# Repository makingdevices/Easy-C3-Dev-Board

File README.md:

<!-- Improved compatibility of back to top link: See: https://github.com/othneildrew/Best-README-Template/pull/73 -->

<!--
*** Thanks for checking out the Best-README-Template. If you have a suggestion
*** that would make this better, please fork the repo and create a pull request
*** or simply open an issue with the tag "enhancement".
*** Don't forget to give the project a star!
*** Thanks again! Now go create something AMAZING! :D
-->

<!-- PROJECT SHIELDS -->
<!--
*** I'm using markdown "reference style" links for readability.
*** Reference links are enclosed in brackets [ ] instead of parentheses ( ).
*** See the bottom of this document for the declaration of the reference variables
*** for contributors-url, forks-url, etc. This is an optional, concise syntax you may use.
*** https://www.markdownguide.org/basic-syntax/#reference-style-links
-->
[![Instagram][ig-shield]][ig-url]
[![PCBWAY][sponsor-shield]][sponsor-url]
[![Stargazers][stars-shield]][stars-url]
[![Issues][issues-shield]][issues-url]
[![LinkedIn][linkedin-shield]][linkedin-url]

<!-- PROJECT LOGO -->
<br />
<div align="center">

<h3 align="center">Making Devices</h3>

  <p align="center">
    Open Source projects where we struggle with engineering, electronics, coding and who knows what else... In this case, The Easy C3 Dev Board is a development board for the esp32 C3 so I can test their capabilities, so hopefully you may find it interesting ;)
  </p>
</div>

<!-- TABLE OF CONTENTS -->
<details>
  <summary>Table of Contents</summary>
  <ol>
    <li>
      <a href="#about-the-project">About The Project</a>
      <ul>
        <li><a href="#built-with">Built With</a></li>
      </ul>
    </li>
    <li>
      <a href="#Build-one">Build one</a>
      <ul>
      </ul>
    </li>
    <li><a href="#usage">Usage</a></li>
    <li><a href="#roadmap">Roadmap</a></li>
    <li><a href="#license">License</a></li>
    <li><a href="#contact">Contact</a></li>
    <li><a href="#Sponsor">Sponsor</a></li>
  </ol>
</details>

<!-- ABOUT THE PROJECT -->
## About The Project

[![Bytes Counter Shot][product-screenshot]](https://github.com/makingdevices/Easy-C3-Dev-Board)

The Easy C3 Dev Board is a esp32 C3 based development board to test this microcontroller.

This device is under development, so I do encourage you to not assembly, order any PCB or use any software from this repository until the project is finished.

<p align="right">(<a href="#readme-top">back to top</a>)</p>

### Built With

[![Kicad][kicad-shield]][kicad-url]
[![SPONSOR][sponsor-icon]][sponsor-url]

<p align="right">(<a href="#readme-top">back to top</a>)</p>

<!-- GETTING STARTED -->

## Build one
NOT RECOMMENDED AS THE DEVICE IS UNDER DEVELOPMENT

<p align="right">(<a href="#readme-top">back to top</a>)</p>

<!-- USAGE EXAMPLES -->
## Usage

Instructions of use:

- Not tested

<p align="right">(<a href="#readme-top">back to top</a>)</p>

<!-- ROADMAP -->
## Roadmap

- [ ] Assembly project.
- [ ] Test/validate the board

See the [open issues](https://github.com/makingdevices/Easy-C3-Dev-Board/issues) for a full list of proposed features (and known issues).

State: Project <b>UNFINISHED</b> - 08/01/2023

Priority: <b>Medium</b>

<p align="right">(<a href="#readme-top">back to top</a>)</p>

<!-- LICENSE -->
## License

Distributed under three licenses:
- [Hardware](/License/HW_cern_ohl_s_v2.pdf)
- [Software](/License/SW_GPLv3.0.txt)
- [Documentation](/License/Documentation_CC-BY-SA-4.0.txt)

[![GPL v3 License][license-shield]][license-url] 
<p align="right">(<a href="#readme-top">back to top</a>)</p>

<!-- CONTACT -->
## Contact

Making Devices - [@MakingDevices](https://www.instagram.com/makingdevices/)

Project Link: [https://github.com/makingdevices/OpenReflowPlate](https://github.com/makingdevices/Easy-C3-Dev-Board/)

Other Links: [LinkTree](https://makingdevices.com/links/)

<p align="right">(<a href="#readme-top">back to top</a>)</p>

<!-- MARKDOWN LINKS & IMAGES -->
<!-- https://www.markdownguide.org/basic-syntax/#reference-style-links -->
[contributors-shield]: https://img.shields.io/github/contributors/makingdevices/Easy-C3-Dev-Board.svg?style=for-the-badge
[contributors-url]: https://github.com/makingdevices/Easy-C3-Dev-Board/graphs/contributors
[forks-shield]: https://img.shields.io/github/forks/makingdevices/Easy-C3-Dev-Board.svg?style=for-the-badge
[forks-url]: https://github.com/makingdevices/Easy-C3-Dev-Board/network/members
[stars-shield]: https://img.shields.io/github/stars/makingdevices/Easy-C3-Dev-Board.svg?style=for-the-badge
[stars-url]: https://github.com/makingdevices/Easy-C3-Dev-Board/stargazers
[issues-shield]: https://img.shields.io/github/issues/makingdevices/Easy-C3-Dev-Board.svg?style=for-the-badge
[issues-url]: https://github.com/makingdevices/Easy-C3-Dev-Board/issues
[license-shield]: /images/license.png
[license-url]: https://github.com/makingdevices/Easy-C3-Dev-Board/tree/main/License
[linkedin-shield]: https://img.shields.io/badge/-LinkedIn-black.svg?style=for-the-badge&logo=linkedin&colorB=555
[linkedin-url]: https://www.linkedin.com/company/making-devices/
[sponsor-shield]: https://img.shields.io/badge/SPONSOR-PCBWAY-black.svg?style=for-the-badge&colorB=1200
[sponsor-url]: https://www.pcbway.com/?from=makingdevices
[sponsor-screenshot]: /images/PCB_sponsor.png
[product-screenshot]: images/screenshot.jpg
[PIC]: https://img.shields.io/badge/PIC18LF45K50-000000?style=for-the-badge
[PIC-url]: http://ww1.microchip.com/downloads/en/devicedoc/40001350f.pdf
[kicad-shield]: https://img.shields.io/badge/kicad-0b03fc?style=for-the-badge&logo=kicad&logoColor=white
[kicad-url]: https://www.kicad.org/
[YT-screenshot]: images/YT_assembly.PNG
[sponsor-icon]:  https://img.shields.io/badge/-PCBWAY-black.svg?style=for-the-badge&colorB=1200
[ig-shield]: https://img.shields.io/badge/instagram-a83297?style=for-the-badge&logo=instagram&logoColor=white
[ig-url]: https://www.instagram.com/makingdevices/
[MPLAB-C]: https://img.shields.io/badge/MPLAB%20C18-DD0031?style=for-the-badge&logo=C&logoColor=white
[MPLAB-C-url]: https://www.microchip.com/en-us/development-tool/SW006011
[Svelte.dev]: https://img.shields.io/badge/Svelte-4A4A55?style=for-the-badge&logo=svelte&logoColor=FF3E00
[Svelte-url]: https://svelte.dev/
[Laravel.com]: https://img.shields.io/badge/Laravel-FF2D20?style=for-the-badge&logo=laravel&logoColor=white
[Laravel-url]: https://laravel.com
[Bootstrap.com]: https://img.shields.io/badge/Bootstrap-563D7C?style=for-the-badge&logo=bootstrap&logoColor=white
[Bootstrap-url]: https://getbootstrap.com
[JQuery.com]: https://img.shields.io/badge/jQuery-0769AD?style=for-the-badge&logo=jquery&logoColor=white
[JQuery-url]: https://jquery.com

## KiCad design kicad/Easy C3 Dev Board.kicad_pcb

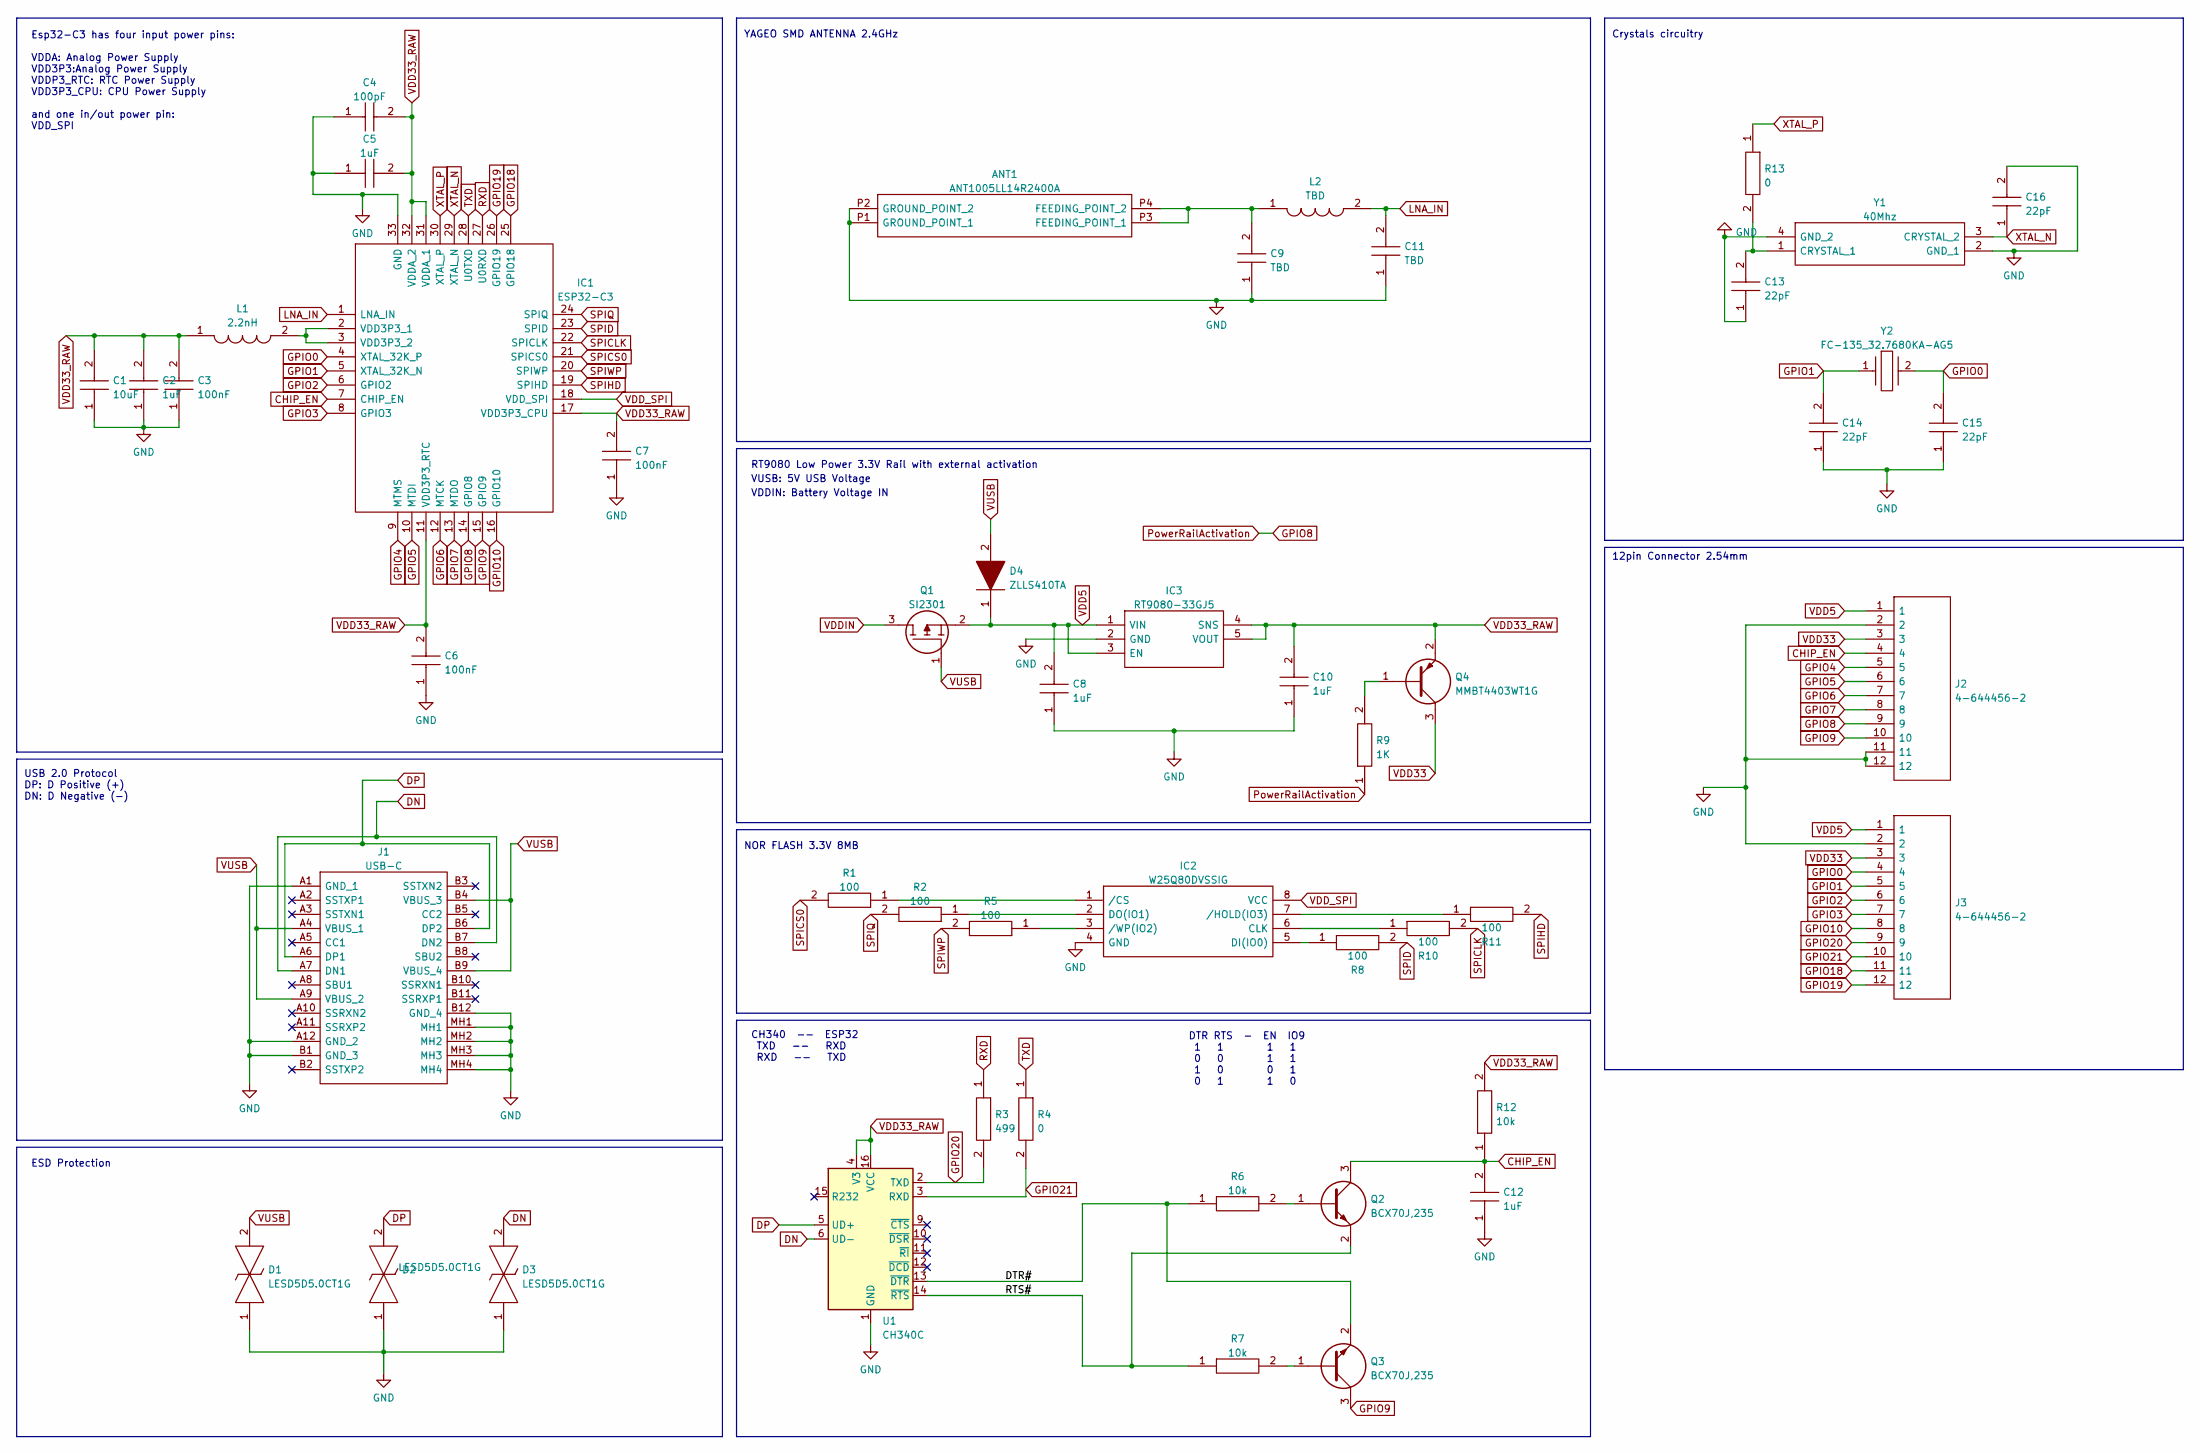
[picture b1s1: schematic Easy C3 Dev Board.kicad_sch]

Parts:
ANT1: ANT1005LL14R2400A; Mouser Part Number 603-ANT1005LL14R2400
C1: 10uF; CAPC2012X140N; Manufacturer_Part_Number C0805C475M8RACTU
C2, C5, C8, C10, C12: 1uF; CAPC2012X140N; Manufacturer_Part_Number C0805C475M8RACTU
C3, C6, C7: 100nF; CAPC2012X140N; Manufacturer_Part_Number C0805C475M8RACTU
C4: 100pF; CAPC2012X140N; Manufacturer_Part_Number C0805C475M8RACTU
C9, C11: TBD; CAPC2012X140N; Manufacturer_Part_Number C0805C475M8RACTU
C13, C14, C15, C16: 22pF; CAPC2012X140N; Manufacturer_Part_Number C0805C475M8RACTU
D1, D2, D3: LESD5D5.0CT1G; SODFL1608X70N; Manufacturer_Part_Number LESD5D5.0CT1G
D4: ZLLS410TA; SOD2513X120N; Manufacturer_Part_Number ZLLS410TA
IC1: ESP32-C3; QFN50P500X500X90-33N-D; Mouser Part Number 356-ESP32-C3
IC2: W25Q80DVSSIG; SOIC127P790X216-8N; Mouser Part Number 454-W25Q80DVSSIG
IC3: RT9080-33GJ5; SOT94P280X100-5N; Manufacturer_Part_Number RT9080-33GJ5
J1: USB-C; 2171830001; Manufacturer_Part_Number 217183-0001
J2, J3: 4-644456-2; HDRV12W67P0X254_1X12_3018X234X1036P; Mouser Part Number 571-4-644456-2
L1: 2.2nH; LQW2BAN11NG00L; Mouser Part Number 81-LQW2BAS2N7J00L
L2: TBD; LQW2BAN11NG00L; Mouser Part Number 81-LQW2BAS2N7J00L
Q1: SI2301; SOT95P240X120-3N; Manufacturer_Part_Number SI2301
Q2, Q3: BCX70J,235; SOT95P230X110-3N; Mouser Part Number 771-BCX70J235
Q4: MMBT4403WT1G; SOT65P220X100-3N; Mouser Part Number 863-MMBT4403WT1G
R1, R2, R5, R8, R10, R11: 100; RESC2012X75N; Manufacturer_Part_Number ERJP6WF1303V
R3: 499; RESC2012X75N; Manufacturer_Part_Number ERJP6WF1303V
R4, R13: 0; RESC2012X75N; Manufacturer_Part_Number ERJP6WF1303V
R6, R7, R12: 10k; RESC2012X75N; Manufacturer_Part_Number ERJP6WF1303V
R9: 1K; RESC2012X75N; Manufacturer_Part_Number ERJP6WF1303V
U1: CH340C; SOIC-16_3.9x9.9mm_P1.27mm
Y1: 40Mhz; CX2520DB12000D0GPSC1; Manufacturer_Part_Number CX2520DB12000D0GPSC1
Y2: FC-135_32.7680KA-AG5; Q13FC1350000200; Manufacturer_Part_Number FC-135_32.7680KA-AG5

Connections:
/DTR#: Q3.2, R6.1, U1.13 (~DTR)
/RTS#: Q2.2, R7.1, U1.14 (~RTS)
CHIP_EN: C12.2, IC1.7 (CHIP_EN), J2.4, Q2.3, R12.1
DN: D3.2, J1.A7 (DN1), J1.B7 (DN2), U1.6 (UD-)
DP: D2.2, J1.A6 (DP1), J1.B6 (DP2), U1.5 (UD+)
GND: ANT1.P1 (GROUND_POINT_1), ANT1.P2 (GROUND_POINT_2), C1.1, C2.1, C3.1, C4.1, C5.1, C6.1, C7.1, C8.1, C9.1, C10.1, C11.1, C12.1, C13.1, C14.1, C15.1, C16.2, D1.1, D2.1, D3.1, IC1.33 (GND), IC2.4 (GND), IC3.2 (GND), J1.A1 (GND_1), J1.A12 (GND_2), J1.B1 (GND_3), J1.B12 (GND_4), J1.MH1, J1.MH2, J1.MH3, J1.MH4, J2.2, J2.11, J2.12, J3.2, U1.1 (GND), Y1.2 (GND_1), Y1.4 (GND_2)
GPIO0: C15.2, IC1.4 (XTAL_32K_P), J3.4, Y2.2
GPIO1: C14.2, IC1.5 (XTAL_32K_N), J3.5, Y2.1
GPIO2: IC1.6 (GPIO2), J3.6
GPIO3: IC1.8 (GPIO3), J3.7
GPIO4: IC1.9 (MTMS), J2.5
GPIO5: IC1.10 (MTDI), J2.6
GPIO6: IC1.12 (MTCK), J2.7
GPIO7: IC1.13 (MTDO), J2.8
GPIO8: IC1.14 (GPIO8), J2.9, R9.1
GPIO9: IC1.15 (GPIO9), J2.10, Q3.3
GPIO10: IC1.16 (GPIO10), J3.8
GPIO18: IC1.25 (GPIO18), J3.11
GPIO19: IC1.26 (GPIO19), J3.12
GPIO20: J3.9, R3.2, U1.2 (TXD)
GPIO21: J3.10, R4.2, U1.3 (RXD)
LNA_IN: C11.2, IC1.1 (LNA_IN), L2.2
unnamed: ANT1.P3 (FEEDING_POINT_1), ANT1.P4 (FEEDING_POINT_2), C9.2, L2.1
unnamed: C13.2, R13.2, Y1.1 (CRYSTAL_1)
unnamed: IC1.2 (VDD3P3_1), IC1.3 (VDD3P3_2), L1.2
unnamed: IC2.1 (/CS), R1.1
unnamed: IC2.2 (DO(IO1)), R2.1
unnamed: IC2.3 (/WP(IO2)), R5.1
unnamed: IC2.5 (DI(IO0)), R8.1
unnamed: IC2.6 (CLK), R10.1
unnamed: IC2.7 (/HOLD(IO3)), R11.1
unnamed: Q2.1, R6.2
unnamed: Q3.1, R7.2
unnamed: Q4.1, R9.2
RXD: IC1.27 (U0RXD), R3.1
SPICLK: IC1.22 (SPICLK), R10.2
SPICS0: IC1.21 (SPICS0), R1.2
SPID: IC1.23 (SPID), R8.2
SPIHD: IC1.19 (SPIHD), R11.2
SPIQ: IC1.24 (SPIQ), R2.2
SPIWP: IC1.20 (SPIWP), R5.2
TXD: IC1.28 (U0TXD), R4.1
VDD5: C8.2, D4.1, IC3.1 (VIN), IC3.3 (EN), J2.1, J3.1, Q1.2
VDD33: J2.3, J3.3, Q4.3
VDD33_RAW: C1.2, C2.2, C3.2, C4.2, C5.2, C6.2, C7.2, C10.2, IC1.11 (VDD3P3_RTC), IC1.17 (VDD3P3_CPU), IC1.31 (VDDA_1), IC1.32 (VDDA_2), IC3.4 (SNS), IC3.5 (VOUT), L1.1, Q4.2, R12.2, U1.4 (V3), U1.16 (VCC)
VDDIN: Q1.3
VDD_SPI: IC1.18 (VDD_SPI), IC2.8 (VCC)
VUSB: D1.2, D4.2, J1.A4 (VBUS_1), J1.A9 (VBUS_2), J1.B4 (VBUS_3), J1.B9 (VBUS_4), Q1.1
XTAL_N: C16.1, IC1.29 (XTAL_N), Y1.3 (CRYSTAL_2)
XTAL_P: IC1.30 (XTAL_P), R13.1

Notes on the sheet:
RT9080 Low Power 3.3V Rail with external activation
DTR RTS - EN IO9 1 1 1 1 0 0 1 1 1 0 0 1 0 1 1 0
NOR FLASH 3.3V 8MB
12pin Connector 2.54mm
VUSB: 5V USB Voltage
ESD Protection
Esp32-C3 has four input power pins: VDDA: Analog Power Supply VDD3P3:Analog Power Supply VDDP3_RTC: RTC Power Supply VDD3P3_CPU: CPU Power Supply and one in/out power pin: VDD_SPI
YAGEO SMD ANTENNA 2.4GHz
CH340 -- ESP32 TXD -- RXD RXD -- TXD
USB 2.0 Protocol DP: D Positive (+) DN: D Negative (-)
Crystals circuitry
VDDIN: Battery Voltage IN

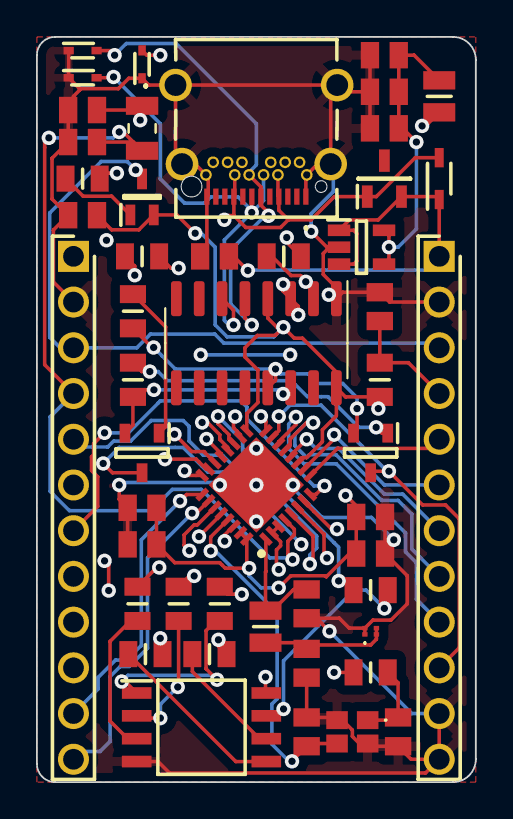
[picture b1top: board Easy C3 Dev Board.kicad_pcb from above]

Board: 4 copper layers, 24.4 x 41.4 mm, 49 parts (0 on the bottom side), 49 nets.

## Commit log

2023-01-07 Update the files
